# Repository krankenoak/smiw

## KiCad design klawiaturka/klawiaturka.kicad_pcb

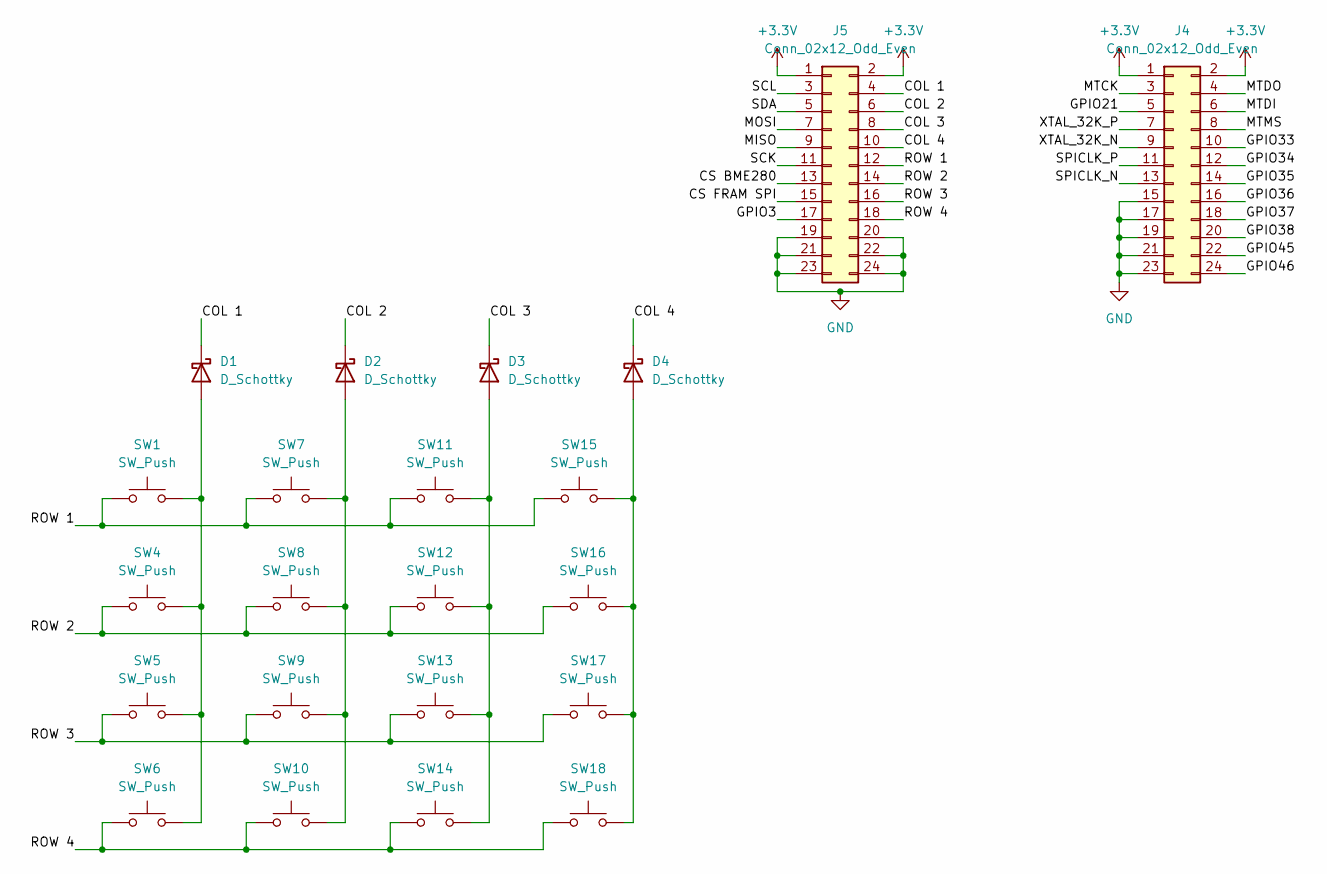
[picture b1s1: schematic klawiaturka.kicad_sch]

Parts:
D1, D2, D3, D4: D_Schottky; D_0603_1608Metric
J4, J5: Conn_02x12_Odd_Even; PinSocket_2x12_P2.54mm_Vertical
SW1, SW4, SW5, SW6, SW7, SW8, SW9, SW10, SW11, SW12, SW13, SW14, SW15, SW16, SW17, SW18: SW_Push; SW_SPST_Omron_B3FS-100xP

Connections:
+3.3V: J4.1, J4.2, J5.1, J5.2
/COL 1: D1.1 (K), J5.4
/COL 2: D2.1 (K), J5.6
/COL 3: D3.1 (K), J5.8
/COL 4: D4.1 (K), J5.10
/CS BME280: J5.13
/CS FRAM SPI: J5.15
/GPIO3: J5.17
/GPIO21: J4.5
/GPIO33: J4.10
/GPIO34: J4.12
/GPIO35: J4.14
/GPIO36: J4.16
/GPIO37: J4.18
/GPIO38: J4.20
/GPIO45: J4.22
/GPIO46: J4.24
/MISO: J5.9
/MOSI: J5.7
/MTCK: J4.3
/MTDI: J4.6
/MTDO: J4.4
/MTMS: J4.8
/ROW 1: J5.12, SW7.1, SW11.1, SW15.1; also elsewhere on the board
/ROW 2: J5.14, SW4.1, SW8.1, SW12.1, SW16.1
/ROW 3: J5.16, SW5.1, SW9.1, SW13.1, SW17.1
/ROW 4: J5.18, SW6.1, SW10.1, SW14.1, SW18.1
/SCK: J5.11
/SCL: J5.3
/SDA: J5.5
/SPICLK_N: J4.13
/SPICLK_P: J4.11
/XTAL_32K_N: J4.9
/XTAL_32K_P: J4.7
GND: J4.15, J4.17, J4.19, J4.21, J4.23, J5.19, J5.20, J5.21, J5.22, J5.23, J5.24
unnamed 35: D1.2 (A), SW4.2, SW5.2, SW6.2; also elsewhere on the board
unnamed: D2.2 (A), SW7.2, SW8.2, SW9.2, SW10.2
unnamed: D3.2 (A), SW11.2, SW12.2, SW13.2, SW14.2
unnamed: D4.2 (A), SW15.2, SW16.2, SW17.2, SW18.2

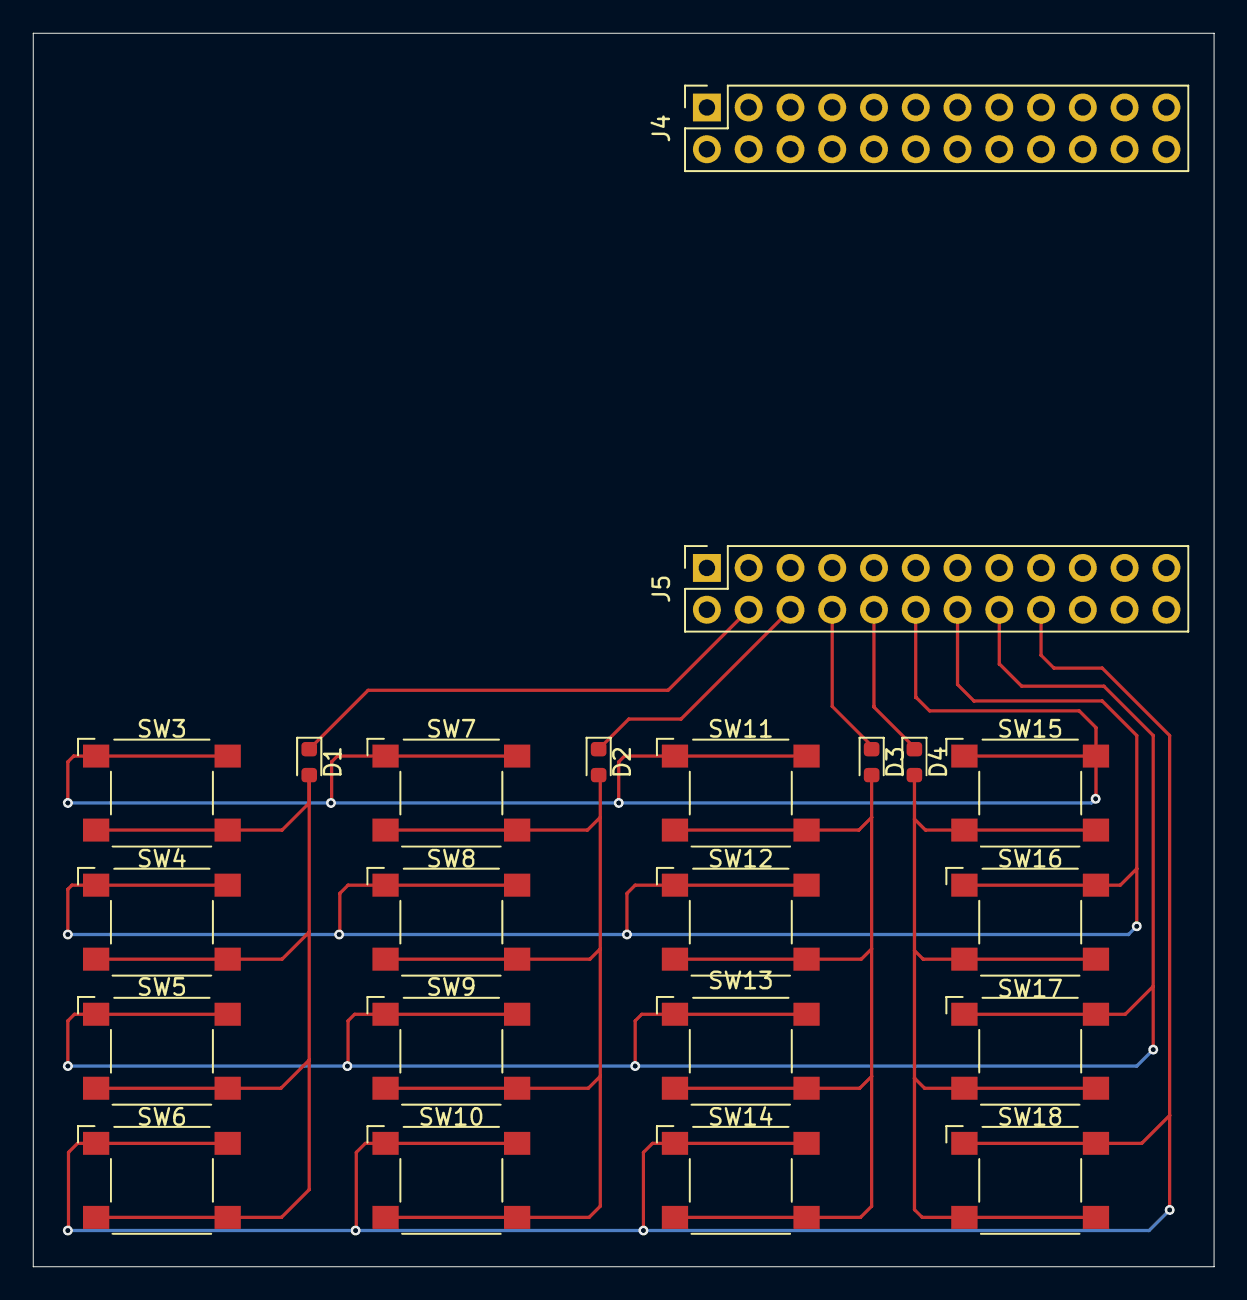
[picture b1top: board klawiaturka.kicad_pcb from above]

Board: 4 copper layers, 71.8 x 75.0 mm, 22 parts (0 on the bottom side), 14 nets.

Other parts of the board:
SW3: SW_Push; SW_SPST_Omron_B3FS-100xP

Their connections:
/ROW 1: SW3.1; also elsewhere on the board
unnamed 35: SW3.2; also elsewhere on the board

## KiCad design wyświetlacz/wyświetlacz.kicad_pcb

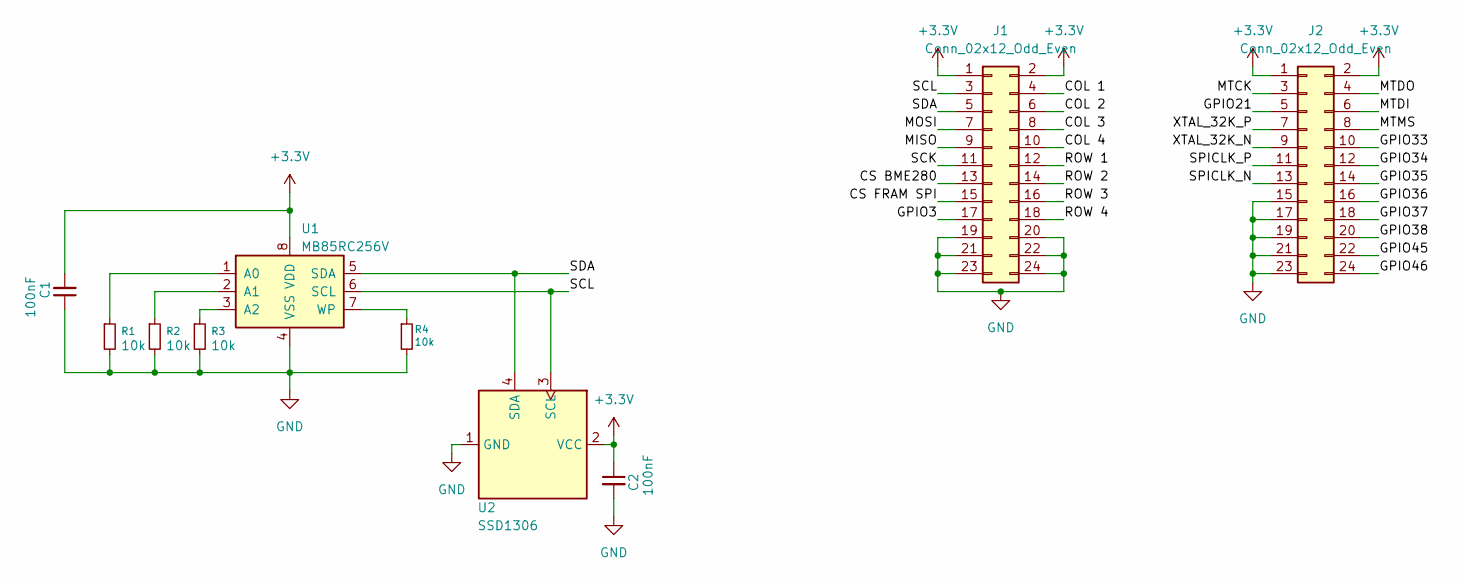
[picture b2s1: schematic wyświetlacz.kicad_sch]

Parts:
C1, C2: 100nF; C_0603_1608Metric
J1, J2: Conn_02x12_Odd_Even; PinSocket_2x12_P2.54mm_Vertical
R1, R2, R3, R4: 10k; R_0603_1608Metric
U1: MB85RC256V; SOIC-8_3.9x4.9mm_P1.27mm
U2: SSD1306; ER_OLEDM0.91_1x-I2C

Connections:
+3.3V: C1.2, C2.1, J1.1, J1.2, J2.1, J2.2, U1.8 (VDD), U2.2 (VCC)
/COL 1: J1.4
/COL 2: J1.6
/COL 3: J1.8
/COL 4: J1.10
/CS BME280: J1.13
/CS FRAM SPI: J1.15
/GPIO3: J1.17
/GPIO21: J2.5
/GPIO33: J2.10
/GPIO34: J2.12
/GPIO35: J2.14
/GPIO36: J2.16
/GPIO37: J2.18
/GPIO38: J2.20
/GPIO45: J2.22
/GPIO46: J2.24
/MISO: J1.9
/MOSI: J1.7
/MTCK: J2.3
/MTDI: J2.6
/MTDO: J2.4
/MTMS: J2.8
/ROW 1: J1.12
/ROW 2: J1.14
/ROW 3: J1.16
/ROW 4: J1.18
/SCK: J1.11
/SCL: J1.3, U1.6 (SCL), U2.3 (SCL)
/SDA: J1.5, U1.5 (SDA), U2.4 (SDA)
/SPICLK_N: J2.13
/SPICLK_P: J2.11
/XTAL_32K_N: J2.9
/XTAL_32K_P: J2.7
GND: C1.1, C2.2, J1.19, J1.20, J1.21, J1.22, J1.23, J1.24, J2.15, J2.17, J2.19, J2.21, J2.23, R1.2, R2.2, R3.2, R4.2, U1.4 (VSS), U2.1 (GND)
unnamed: R1.1, U1.1 (A0)
unnamed: R2.1, U1.2 (A1)
unnamed: R3.1, U1.3 (A2)
unnamed: R4.1, U1.7 (WP)

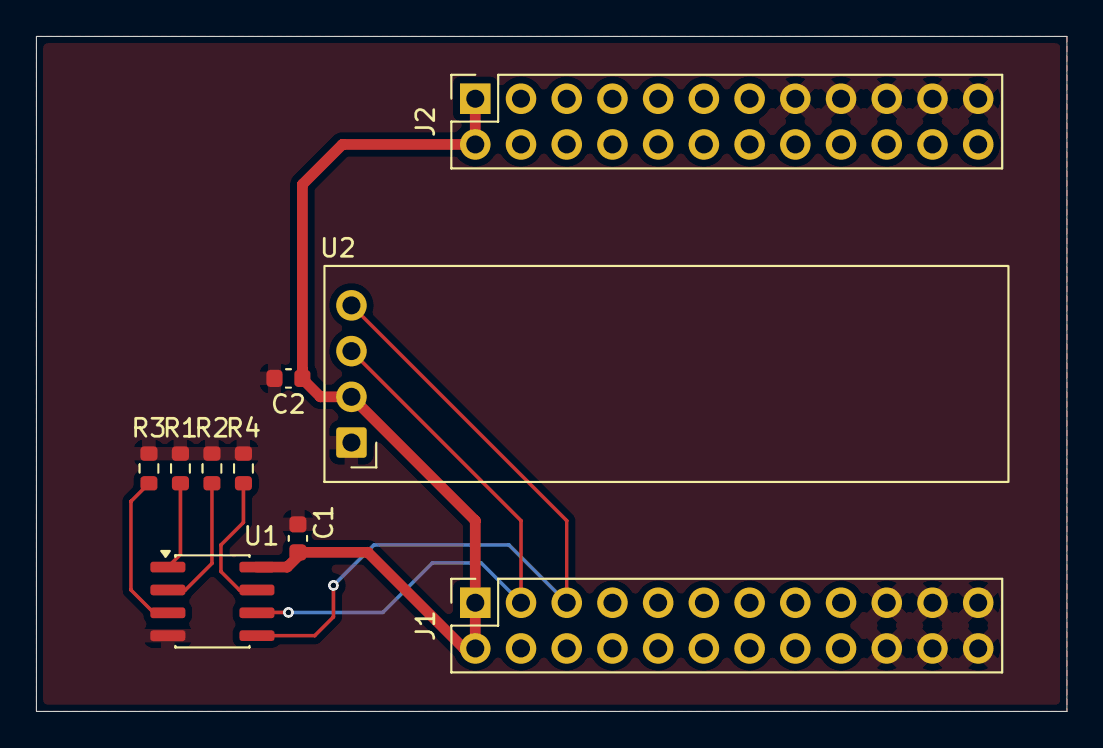
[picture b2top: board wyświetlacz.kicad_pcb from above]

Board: 4 copper layers, 57.2 x 37.5 mm, 10 parts (0 on the bottom side), 8 nets.

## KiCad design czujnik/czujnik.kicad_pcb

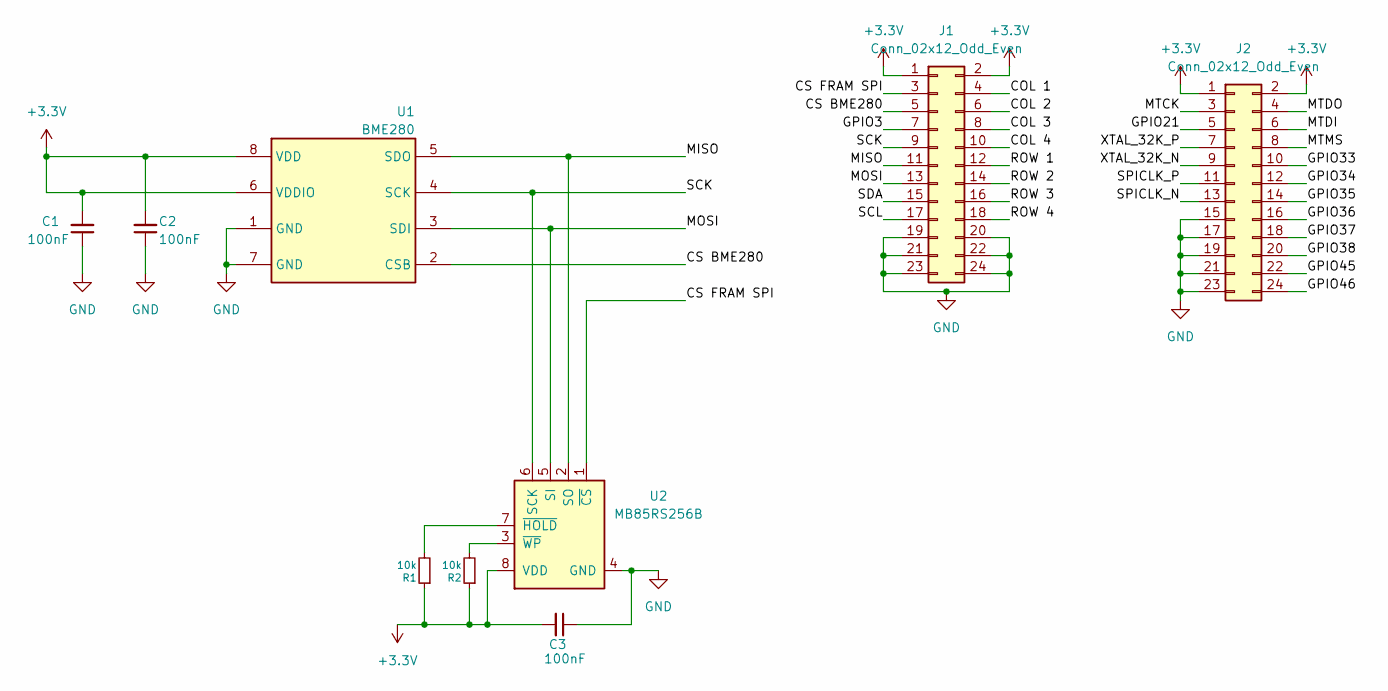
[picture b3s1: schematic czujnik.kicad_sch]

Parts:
C1, C2, C3: 100nF; C_0603_1608Metric
J1, J2: Conn_02x12_Odd_Even; PinSocket_2x12_P2.54mm_Vertical
R1, R2: 10k; R_0603_1608Metric
U1: BME280; Bosch_LGA-8_2.5x2.5mm_P0.65mm_ClockwisePinNumbering
U2: MB85RS256B; SOIC-8_3.9x4.9mm_P1.27mm

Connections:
+3.3V: C1.2, C2.2, C3.2, J1.1, J1.2, J2.1, J2.2, R1.1, R2.1, U1.6 (VDDIO), U1.8 (VDD), U2.8 (VDD)
/COL 1: J1.4
/COL 2: J1.6
/COL 3: J1.8
/COL 4: J1.10
/CS BME280: J1.5, U1.2 (CSB)
/CS FRAM SPI: J1.3, U2.1 (~CS)
/GPIO3: J1.7
/GPIO21: J2.5
/GPIO33: J2.10
/GPIO34: J2.12
/GPIO35: J2.14
/GPIO36: J2.16
/GPIO37: J2.18
/GPIO38: J2.20
/GPIO45: J2.22
/GPIO46: J2.24
/MISO: J1.11, U1.5 (SDO), U2.2 (SO)
/MOSI: J1.13, U1.3 (SDI), U2.5 (SI)
/MTCK: J2.3
/MTDI: J2.6
/MTDO: J2.4
/MTMS: J2.8
/ROW 1: J1.12
/ROW 2: J1.14
/ROW 3: J1.16
/ROW 4: J1.18
/SCK: J1.9, U1.4 (SCK), U2.6 (SCK)
/SCL: J1.17
/SDA: J1.15
/SPICLK_N: J2.13
/SPICLK_P: J2.11
/XTAL_32K_N: J2.9
/XTAL_32K_P: J2.7
GND: C1.1, C2.1, C3.1, J1.19, J1.20, J1.21, J1.22, J1.23, J1.24, J2.15, J2.17, J2.19, J2.21, J2.23, U1.1 (GND), U1.7 (GND), U2.4 (GND)
unnamed: R1.2, U2.7 (~HOLD)
unnamed: R2.2, U2.3 (~WP)

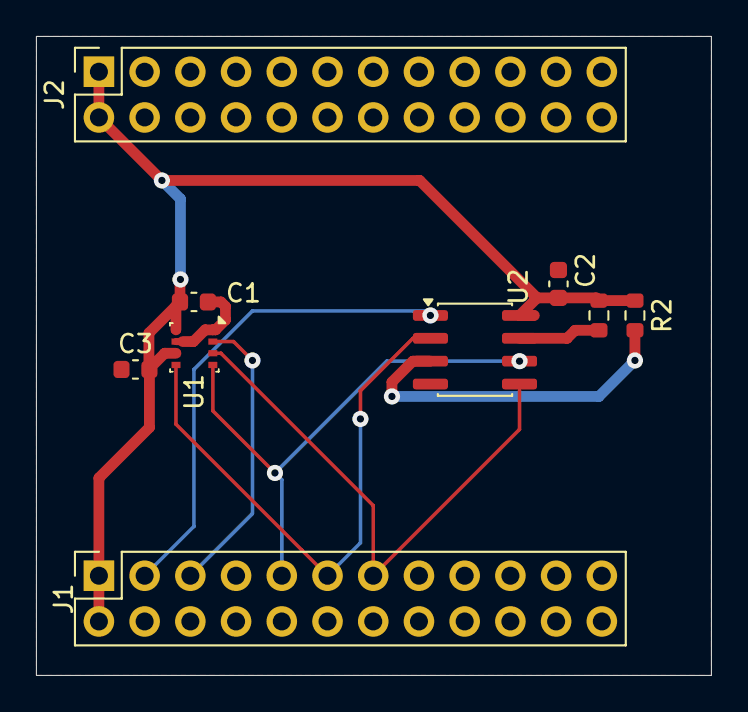
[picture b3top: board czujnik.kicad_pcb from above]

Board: 4 copper layers, 37.5 x 35.5 mm, 9 parts (0 on the bottom side), 9 nets.

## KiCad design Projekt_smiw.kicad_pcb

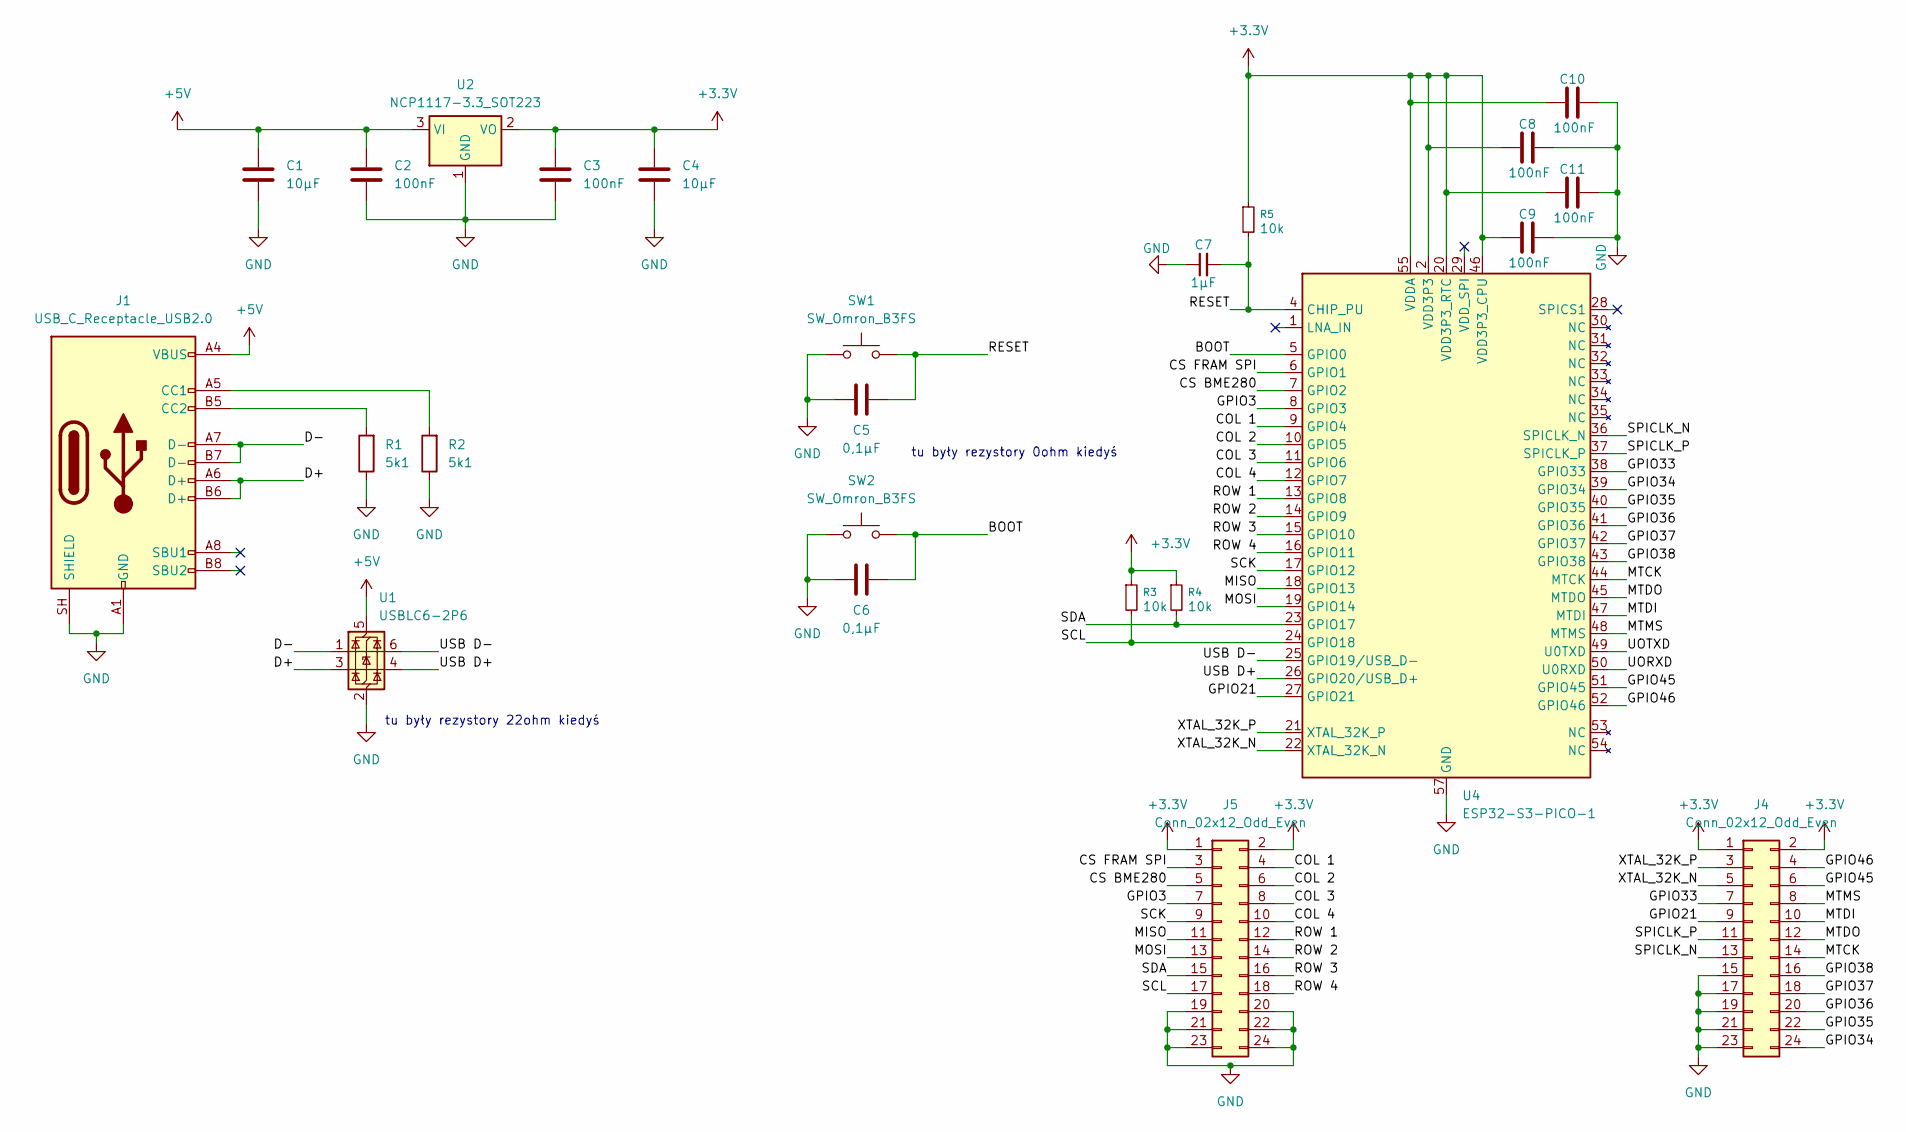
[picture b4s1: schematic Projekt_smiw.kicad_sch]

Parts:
C1, C4: 10μF; C_0805_2012Metric
C2, C3, C8, C9, C10, C11: 100nF; C_0603_1608Metric
C5, C6: 0,1μF; C_0603_1608Metric
C7: 1μF; C_0603_1608Metric
J1: USB_C_Receptacle_USB2.0; USB_C_Receptacle_HRO_TYPE-C-31-M-12
J4, J5: Conn_02x12_Odd_Even; PinSocket_2x12_P2.54mm_Vertical
R1, R2: 5k1; R_0603_1608Metric
R3, R4, R5: 10k; R_0603_1608Metric
SW1, SW2: SW_Omron_B3FS; SW_SPST_Omron_B3FS-100xP
U1: USBLC6-2P6; SOT-666
U2: NCP1117-3.3_SOT223; SOT-223-3_TabPin2
U4: ESP32-S3-PICO-1; QFN-56-1EP_7x7mm_P0.4mm_EP4x4mm

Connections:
+3.3V: C3.1, C4.1, C8.1, C9.1, C10.1, C11.1, J4.1, J4.2, J5.1, J5.2, R3.1, R4.1, R5.1, U2.2 (VO), U4.2 (VDD3P3), U4.3 (VDD3P3), U4.20 (VDD3P3_RTC), U4.46 (VDD3P3_CPU), U4.55 (VDDA), U4.56 (VDDA)
+5V: C1.1, C2.1, J1.A4 (VBUS), J1.A9 (VBUS), J1.B4 (VBUS), J1.B9 (VBUS), U1.5 (VBUS), U2.3 (VI)
/BOOT: C6.2, SW2.2, U4.5 (GPIO0)
/COL 1: J5.4, U4.9 (GPIO4)
/COL 2: J5.6, U4.10 (GPIO5)
/COL 3: J5.8, U4.11 (GPIO6)
/COL 4: J5.10, U4.12 (GPIO7)
/CS BME280: J5.5, U4.7 (GPIO2)
/CS FRAM SPI: J5.3, U4.6 (GPIO1)
/D+: J1.A6 (D+), J1.B6 (D+), U1.3 (I/O2)
/D-: J1.A7 (D-), J1.B7 (D-), U1.1 (I/O1)
/GPIO3: J5.7, U4.8 (GPIO3)
/GPIO21: J4.9, U4.27 (GPIO21)
/GPIO33: J4.7, U4.38 (GPIO33)
/GPIO34: J4.24, U4.39 (GPIO34)
/GPIO35: J4.22, U4.40 (GPIO35)
/GPIO36: J4.20, U4.41 (GPIO36)
/GPIO37: J4.18, U4.42 (GPIO37)
/GPIO38: J4.16, U4.43 (GPIO38)
/GPIO45: J4.6, U4.51 (GPIO45)
/GPIO46: J4.4, U4.52 (GPIO46)
/MISO: J5.11, U4.18 (GPIO13)
/MOSI: J5.13, U4.19 (GPIO14)
/MTCK: J4.14, U4.44 (MTCK)
/MTDI: J4.10, U4.47 (MTDI)
/MTDO: J4.12, U4.45 (MTDO)
/MTMS: J4.8, U4.48 (MTMS)
/RESET: C5.2, C7.2, R5.2, SW1.2, U4.4 (CHIP_PU)
/ROW 1: J5.12, U4.13 (GPIO8)
/ROW 2: J5.14, U4.14 (GPIO9)
/ROW 3: J5.16, U4.15 (GPIO10)
/ROW 4: J5.18, U4.16 (GPIO11)
/SCK: J5.9, U4.17 (GPIO12)
/SCL: J5.17, R3.2, U4.24 (GPIO18)
/SDA: J5.15, R4.2, U4.23 (GPIO17)
/SPICLK_N: J4.13, U4.36 (SPICLK_N)
/SPICLK_P: J4.11, U4.37 (SPICLK_P)
/UORXD: U4.50 (U0RXD)
/UOTXD: U4.49 (U0TXD)
/USB D+: U1.4 (I/O2), U4.26 (GPIO20/USB_D+)
/USB D-: U1.6 (I/O1), U4.25 (GPIO19/USB_D-)
/XTAL_32K_N: J4.5, U4.22 (XTAL_32K_N)
/XTAL_32K_P: J4.3, U4.21 (XTAL_32K_P)
GND: C1.2, C2.2, C3.2, C4.2, C5.1, C6.1, C7.1, C8.2, C9.2, C10.2, C11.2, J1.A1 (GND), J1.A12 (GND), J1.B1 (GND), J1.B12 (GND), J1.SH (SHIELD), J4.15, J4.17, J4.19, J4.21, J4.23, J5.19, J5.20, J5.21, J5.22, J5.23, J5.24, R1.1, R2.1, SW1.1, SW2.1, U1.2 (GND), U2.1 (GND), U4.57 (GND)
unnamed: J1.A5 (CC1), R2.2
unnamed: J1.B5 (CC2), R1.2

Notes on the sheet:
tu były rezystory 22ohm kiedyś
tu były rezystory 0ohm kiedyś

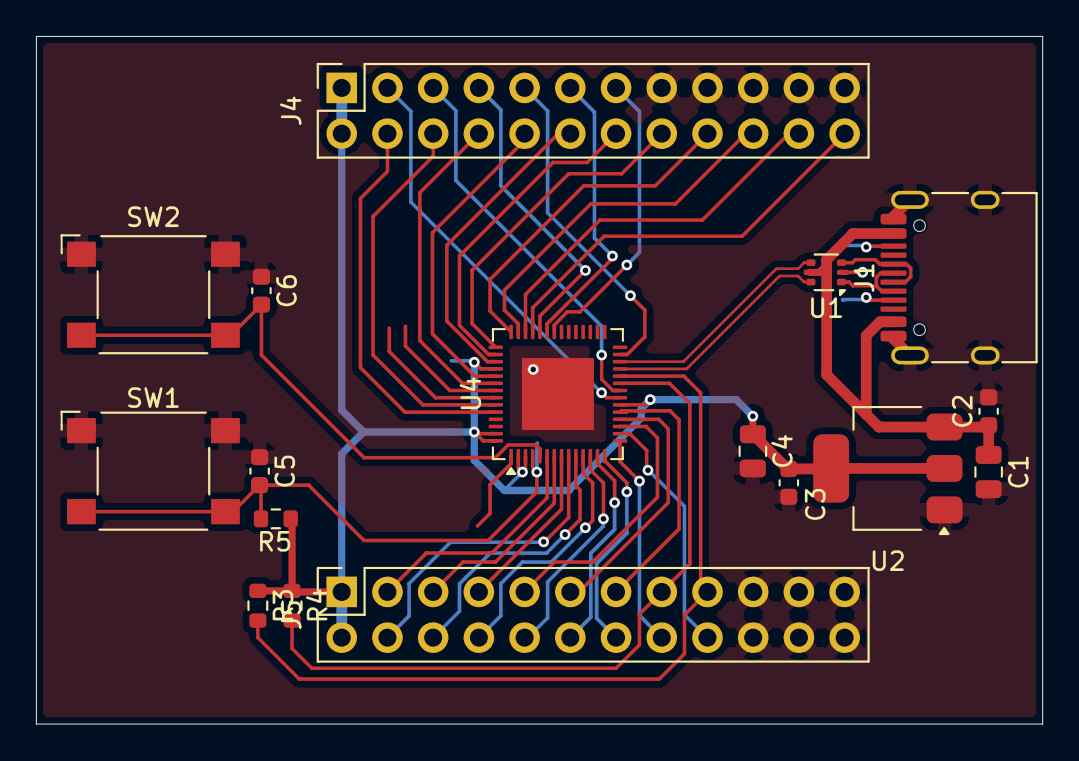
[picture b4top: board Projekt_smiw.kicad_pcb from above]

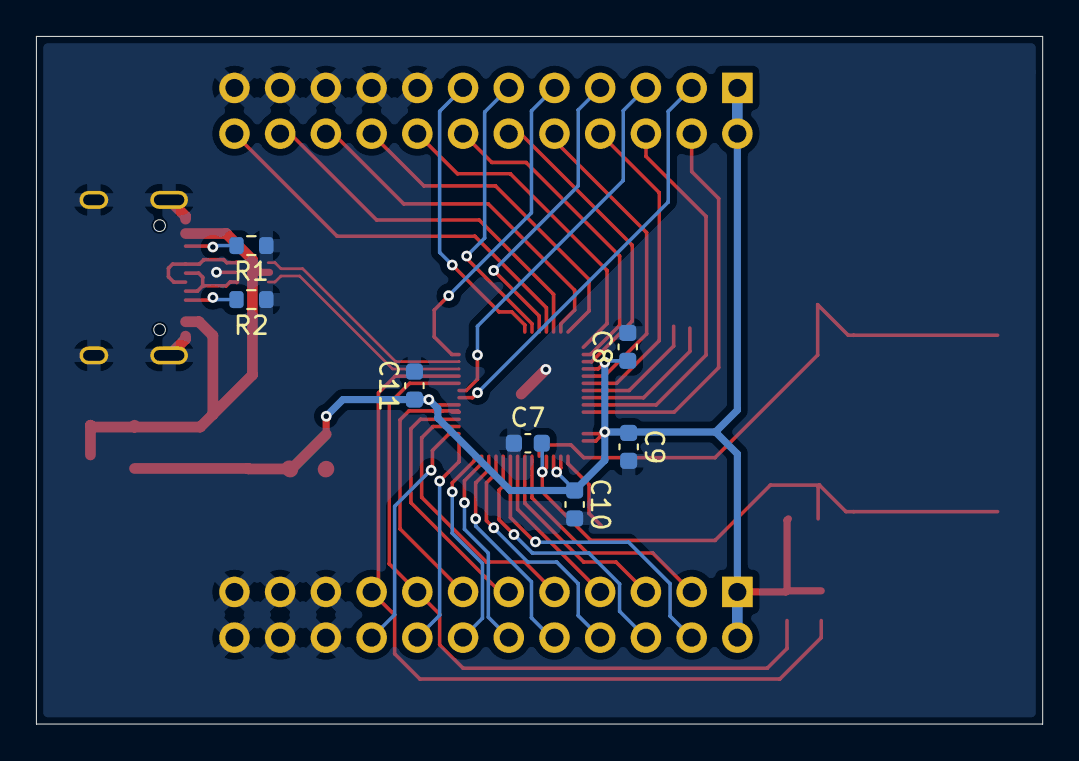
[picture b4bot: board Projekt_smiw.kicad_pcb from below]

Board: 4 copper layers, 55.9 x 38.2 mm, 24 parts (7 on the bottom side), 44 nets.

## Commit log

2026-05-29 0101
2026-05-31 Pinout dla ESP32
2026-06-09 wyswietlacz 1
2026-06-10 Test
2026-06-10 Orange 21.37
2026-06-10 Orange 21.38
2026-06-10 Orange 21.39
2026-06-10 USB C update
2026-06-10 szczerze nie pamiętam co się tutaj zmieniło
2026-06-11 małe zmiany poprawki dsagolih
2026-06-11 dodano kondesnatory 100nF
2026-06-11 footprinty all, aheoi;rthipoawert;hiogsedho;i yay Halo? Schemat zrobiony ^^ pewnie nie
2026-06-13 awetg
2026-06-13 awetg2
2026-06-13 PCB project procesor
2026-06-13 wielka zmiena 2137
2026-06-13 czujnik pcb
2026-06-13 pvcv1
2026-06-13 :3 x2
2026-06-13 Płytka PCB z klawiaturki v1
2026-06-14 Zmianakonnektora
2026-06-14 Zmianakonnektorav2
2026-06-14 Zmianakonnektorav3
2026-06-14 Zmianakonnektorav4
2026-06-14 poprawkaconnector
2026-06-14 prosze aby nie było konlfikut panie Bożę danke
2026-06-14 KlawiaturkaV2
2026-06-14 zegar tesz
